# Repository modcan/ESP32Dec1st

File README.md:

# ESP32Dec1st
last try to get a new esp32 repo going

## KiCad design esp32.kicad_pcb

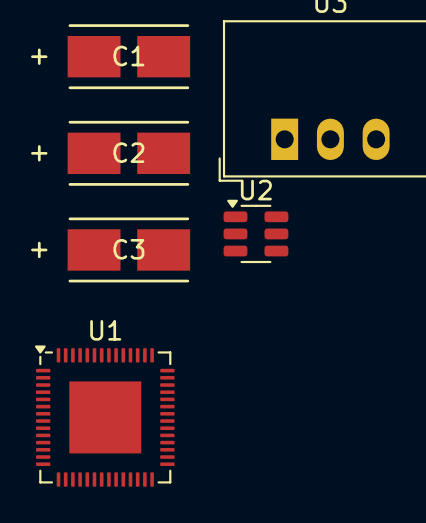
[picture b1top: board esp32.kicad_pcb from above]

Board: 2 copper layers, 6 parts (0 on the bottom side), 3 nets, no tracks yet.

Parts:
C1, C2, C3: T491C106M025AT7280; 10uFtantcap
U1: ESP32-S3; QFN-56-1EP_7x7mm_P0.4mm_EP4x4mm
U2: AAT1217IGU-3.3; SOT-23-6
U3: R-78E3.3-1.0; Converter_DCDC_RECOM_R-78E-0.5_THT

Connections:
unnamed: U1.2 (VDD3P3), U1.3 (VDD3P3)
unnamed: U1.55 (VDDA), U1.56 (VDDA)
unnamed: C1.1, U3.3 (OUT)

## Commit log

2025-12-02 addedstm32F413
2025-12-02 lastest updates
2025-12-06 recloned first commit
2025-12-09 added psucomponets to esp32 IC
2025-12-09 loaded the power symbol library back in
2025-12-12 ADDED PINS TO ESP32 SYMBOL
2025-12-12 added revised esp32 rto common library
2025-12-12 fixed the esp32 footprint
2025-12-13 added footprint for au88c codec
